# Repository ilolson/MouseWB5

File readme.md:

# MouseWB5 
40mm x 65.5mm Mini RC car inspired by half size micro mouse.
It is powered by the STM32WB5 precertified wireless module.
It uses STSPIN240 motor drivers to power four small coreless DC motors.
Contains the LSM6DSO as an IMU, and has headers for an additional fan motor for a suction mechanism.
SPI and I2C module connections for future VL53 lidar sensors, as well as programmable drift lights and turn signals. 
Includes a battery charging circuit and can be programmed via the TC2030 debug connector.

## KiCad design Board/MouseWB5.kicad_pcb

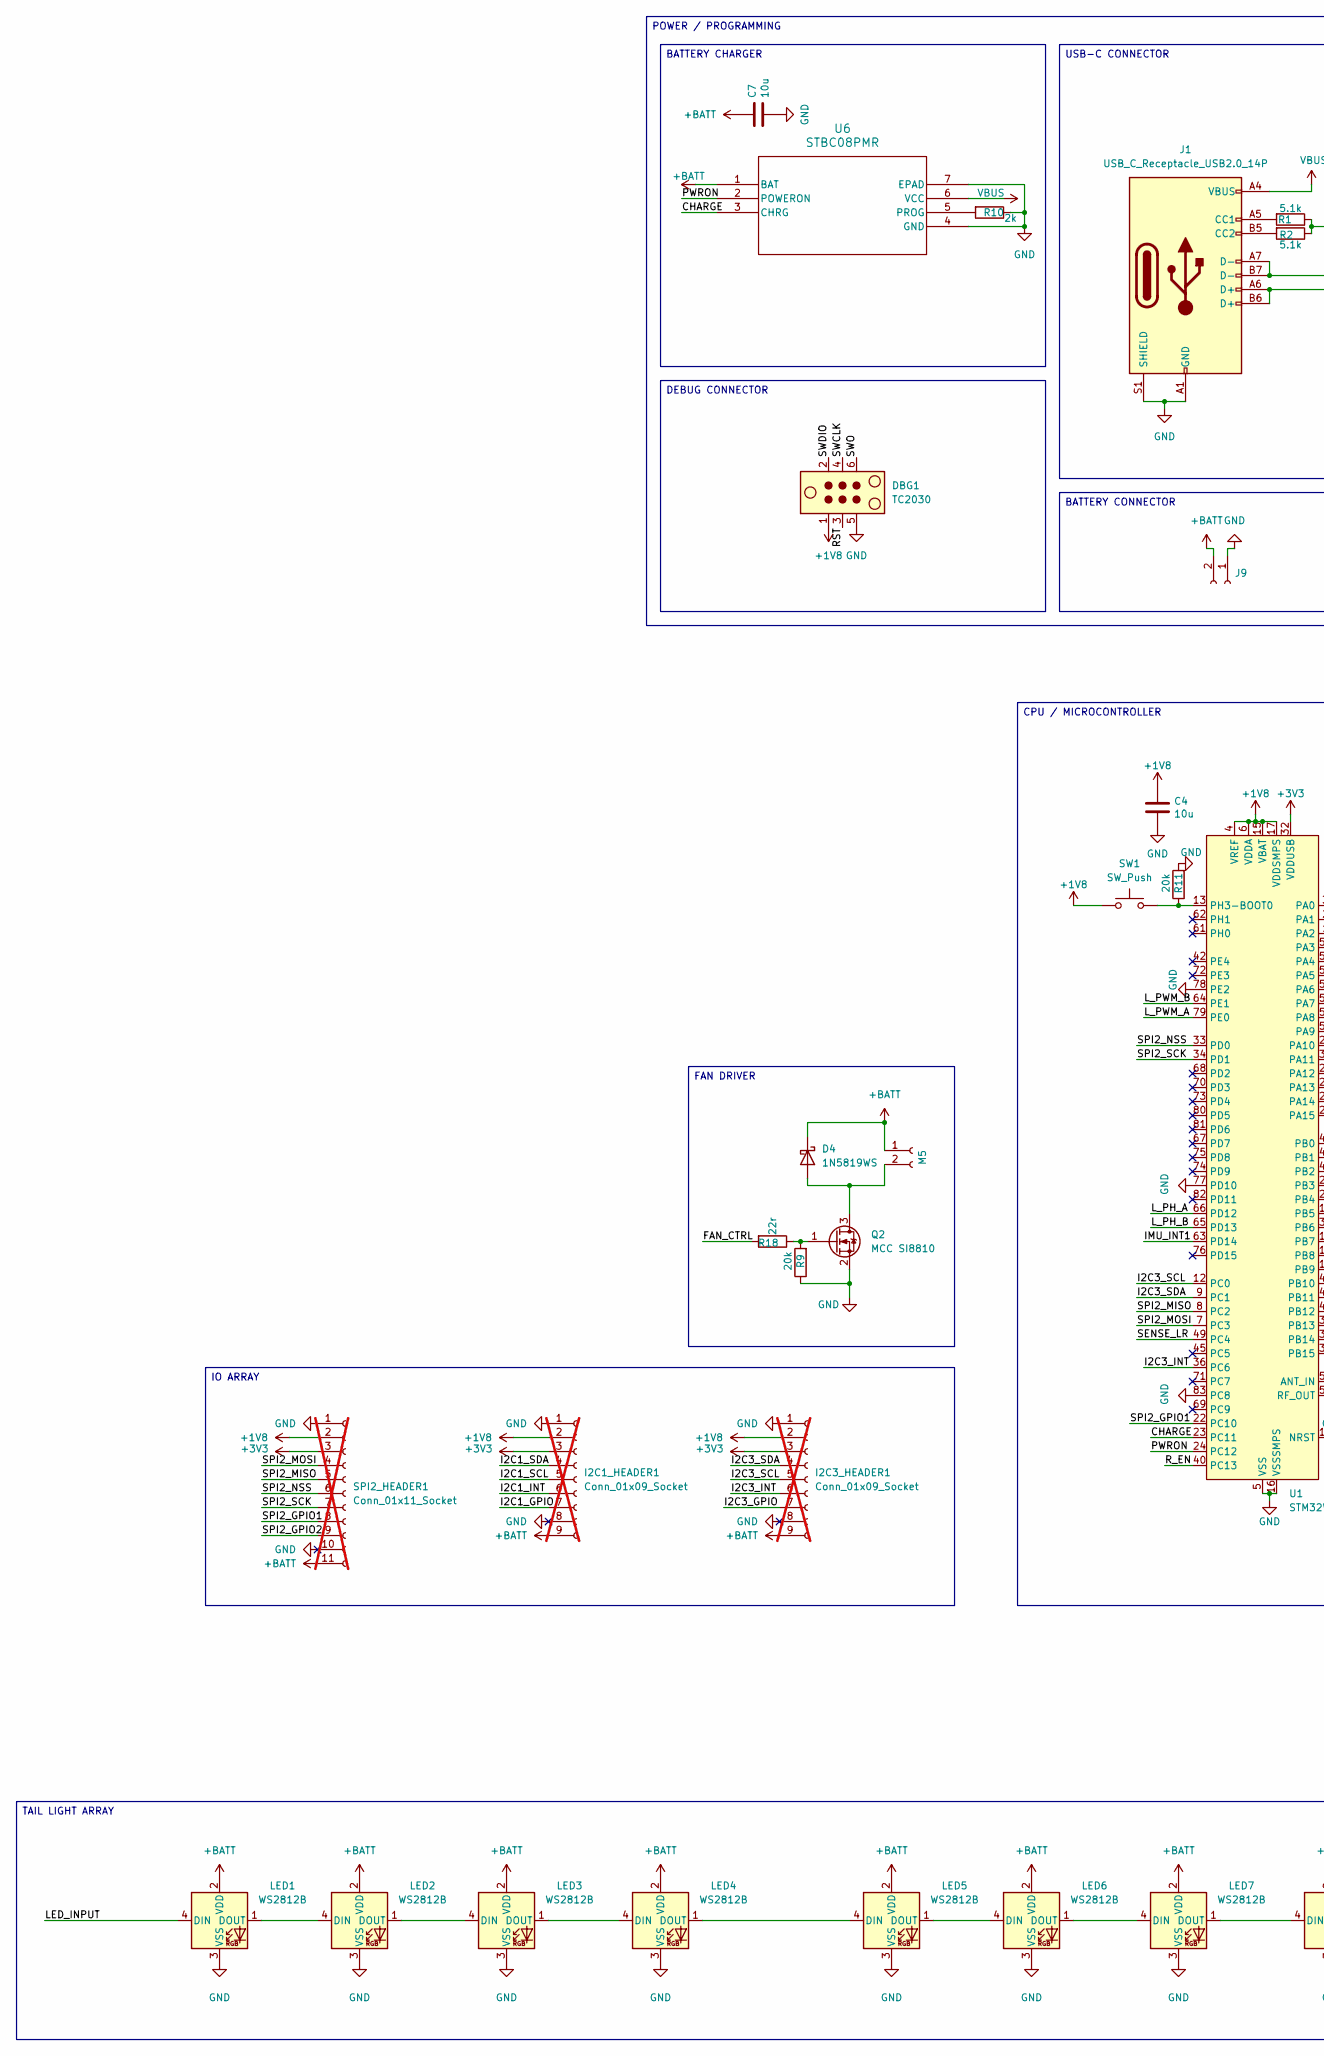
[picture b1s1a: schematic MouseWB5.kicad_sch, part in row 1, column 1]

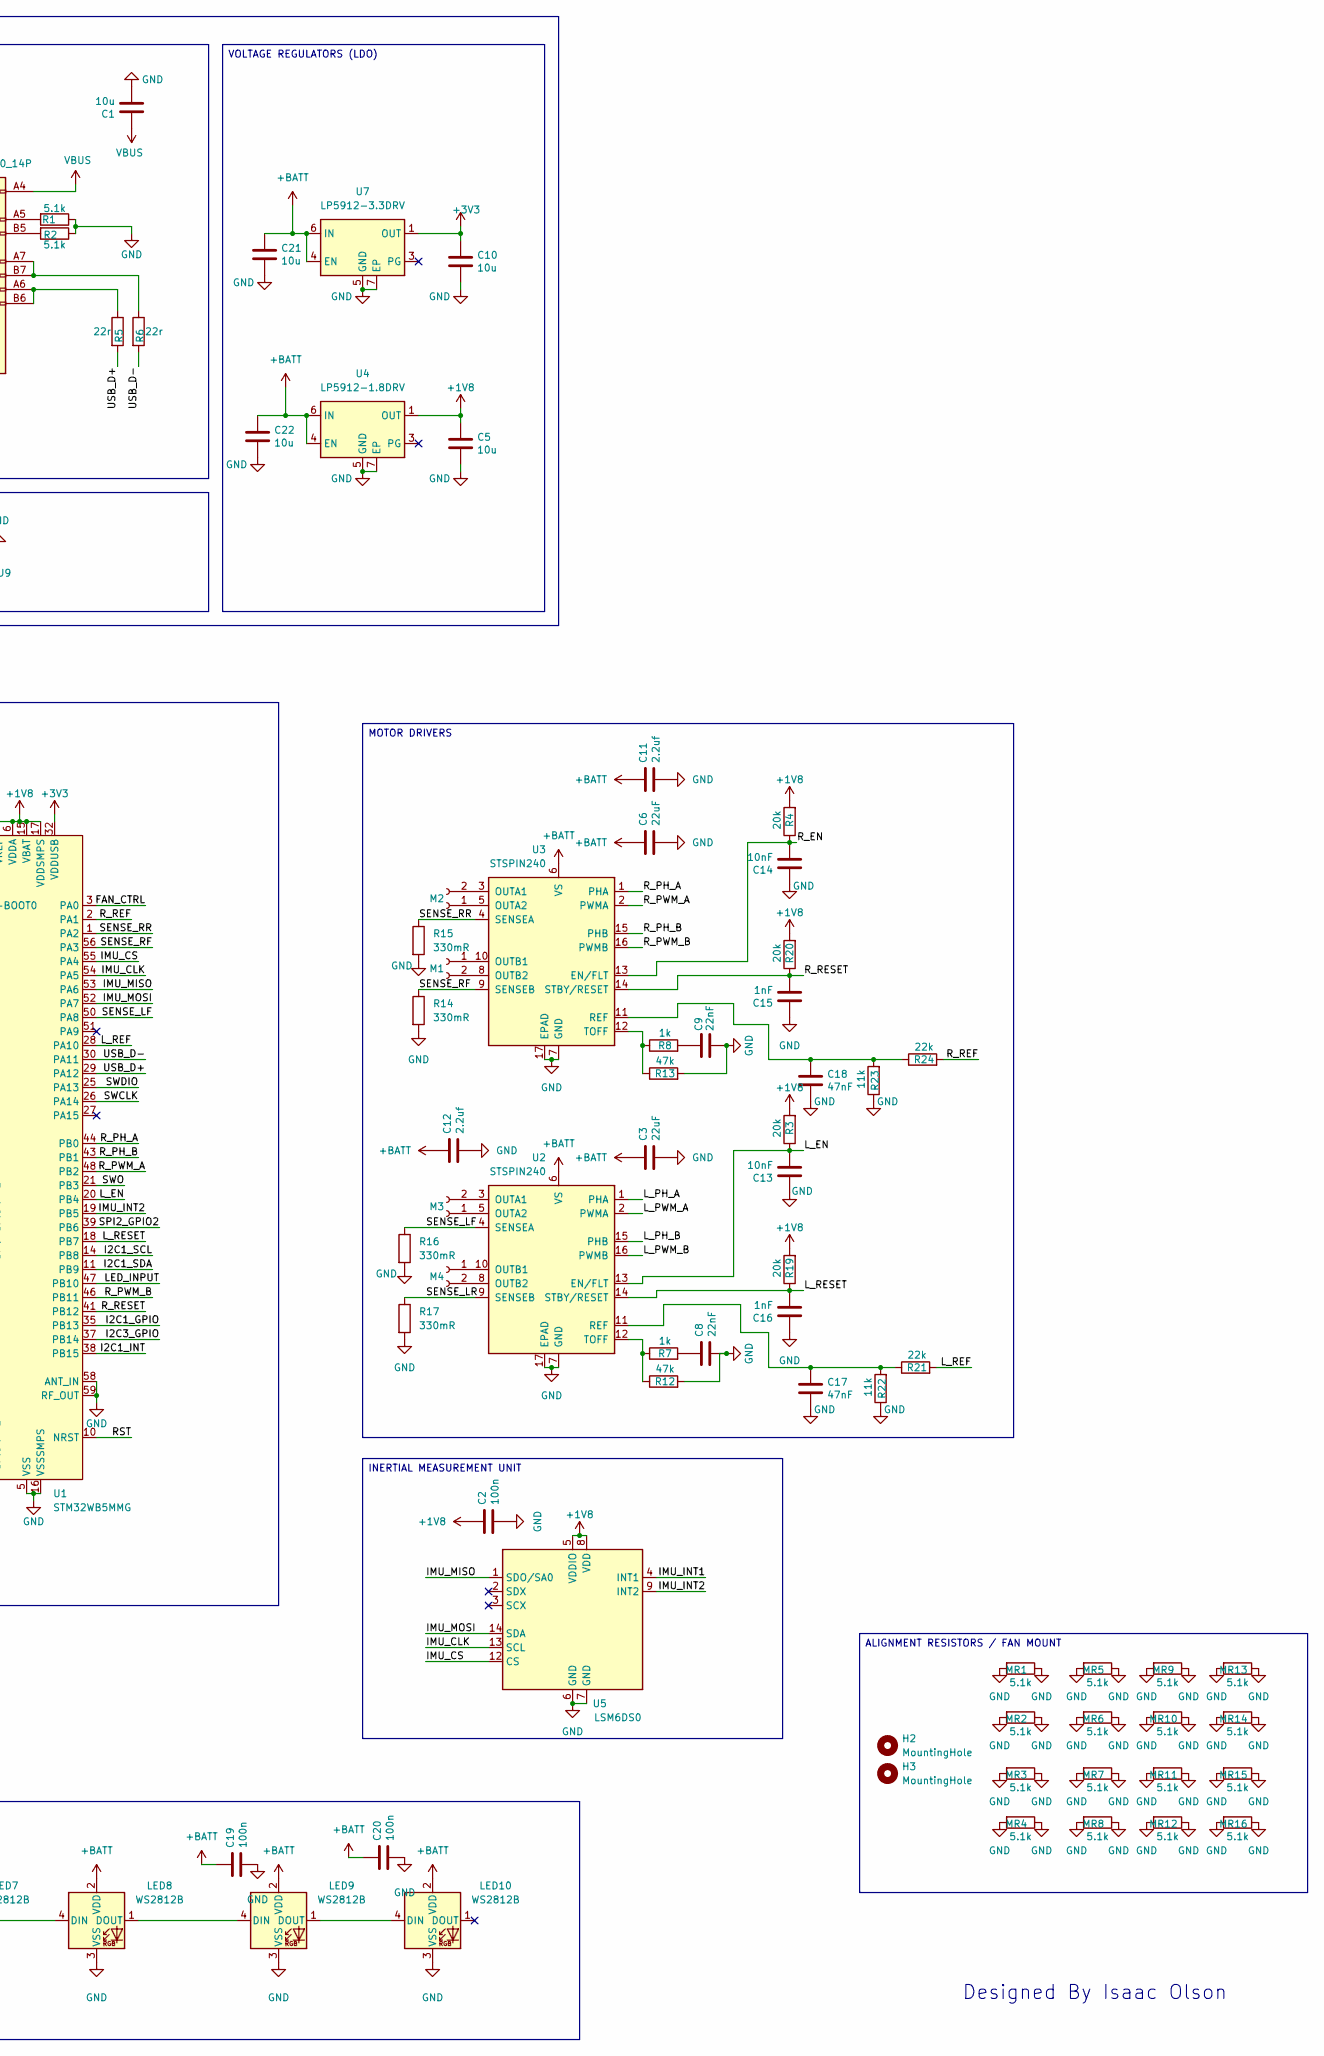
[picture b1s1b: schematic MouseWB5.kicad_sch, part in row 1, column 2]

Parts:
C1, C4, C5, C7, C10, C21, C22: 10u; C_0805_2012Metric; LCSC C408141
C2, C19, C20: 100n; C_0402_1005Metric; LCSC C1525
C3, C6: 22uF; C_0805_2012Metric; LCSC C602037
C8, C9: 22nF; C_0402_1005Metric; LCSC C337699
C11, C12: 2.2uf; C_0402_1005Metric; LCSC C170151
C13, C14: 10nF; C_0402_1005Metric; LCSC C15195
C15, C16: 1nF; C_0402_1005Metric; LCSC C77018
C17, C18: 47nF; C_0402_1005Metric; LCSC C82219
D4: 1N5819WS; D_SOD-323; LCSC C191023
DBG1: TC2030; Tag-Connect_TC2030-IDC-NL_2x03_P1.27mm_Vertical
H2, H3: MountingHole; MountingHole_2.1mm
I2C1_HEADER1, I2C3_HEADER1: Conn_01x09_Socket; PinHeader_1x09_P1.00mm_Vertical; not fitted
J1: USB_C_Receptacle_USB2.0_14P; USB_C_Receptacle_HRO_TYPE-C-31-M-12; LCSC C165948
J9: Conn_01x02_Socket; JST_GH_BM02B-GHS-TBT_1x02-1MP_P1.25mm_Vertical; LCSC C161690
LED1, LED2, LED3, LED4, LED5, LED6, LED7, LED8: WS2812B; LED-SMD_4P-L1.0-W1.0-TL_XL-1010RGBC-WS2812B; LCSC C5349953
LED9, LED10: WS2812B; 1010ws2812; LCSC C5349953
M1, M2, M3, M4, M5: Conn_01x02_Socket; JST_GH_BM02B-GHS-TBT_1x02-1MP_P1.25mm_Vertical; LCSC C161690
MR1, MR2, MR3, MR4, MR5, MR6, MR7, MR8, MR9, MR10, MR11, MR12, MR13, MR14, MR15, MR16: 5.1k; R_0402_1005Metric; LCSC C105872
Q2: MCC SI8810; SOT-23; LCSC C669009
R1, R2: 5.1k; R_0402_1005Metric; LCSC C105872
R3, R4, R9, R11, R19, R20: 20k; R_0402_1005Metric; LCSC C93942
R5, R6, R18: 22r; R_0201_0603Metric; LCSC C270355
R7, R8: 1k; R_0402_1005Metric; LCSC C106235
R10: 2k; R_0402_1005Metric; LCSC C4109
R12, R13: 47k; R_0402_1005Metric; LCSC C93943
R14, R15, R16, R17: 330mR; R_1206_3216Metric_Pad1.30x1.75mm_HandSolder; LCSC C2932844
R21, R24: 22k; R_0402_1005Metric; LCSC C82868
R22, R23: 11k; R_0402_1005Metric; LCSC C25749
SPI2_HEADER1: Conn_01x11_Socket; PinHeader_1x11_P1.00mm_Vertical; not fitted
SW1: SW_Push; TS-1088-AR02016; LCSC C455280
U1: STM32WB5MMG; ST-SiP-LGA-86-11x7.3mm; LCSC C5184586
U2, U3: STSPIN240; VQFN-16-1EP_3x3mm_P0.5mm_EP1.8x1.8mm; LCSC C962258
U4: LP5912-1.8DRV; WSON-6-1EP_2x2mm_P0.65mm_EP1x1.6mm_ThermalVias; LCSC C2876234
U5: LSM6DS0; LGA-14_3x2.5mm_P0.5mm_LayoutBorder3x4y; LCSC C481766
U6: STBC08PMR; DFN6_3X3_STM; LCSC C262929
U7: LP5912-3.3DRV; WSON-6-1EP_2x2mm_P0.65mm_EP1x1.6mm_ThermalVias; LCSC C524780

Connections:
+1V8: C2.1, C4.1, C5.1, DBG1.1, I2C1_HEADER1.2, I2C3_HEADER1.2, R3.2, R4.2, R19.2, R20.2, SPI2_HEADER1.2, SW1.1, U1.4 (VREF), U1.6 (VDDA), U1.15 (VBAT), U1.17 (VDDSMPS), U4.1 (OUT), U5.5 (VDDIO), U5.8 (VDD)
+3V3: C10.1, I2C1_HEADER1.3, I2C3_HEADER1.3, SPI2_HEADER1.3, U1.32 (VDDUSB), U7.1 (OUT)
+BATT: C3.1, C6.1, C7.1, C11.1, C12.1, C19.1, C20.1, C21.1, C22.1, D4.1 (K), I2C1_HEADER1.9, I2C3_HEADER1.9, J9.2, LED1.2 (VDD), LED2.2 (VDD), LED3.2 (VDD), LED4.2 (VDD), LED5.2 (VDD), LED6.2 (VDD), LED7.2 (VDD), LED8.2 (VDD), LED9.2 (VDD), LED10.2 (VDD), M5.1, SPI2_HEADER1.11, U2.6 (VS), U3.6 (VS), U4.4 (EN), U4.6 (IN), U6.1 (BAT), U7.4 (EN), U7.6 (IN)
/CHARGE: U1.23 (PC11), U6.3 (CHRG)
/FAN_CTRL: R18.2, U1.3 (PA0)
/I2C1_GPIO: I2C1_HEADER1.7, U1.35 (PB13)
/I2C1_INT: I2C1_HEADER1.6, U1.38 (PB15)
/I2C1_SCL: I2C1_HEADER1.5, U1.14 (PB8)
/I2C1_SDA: I2C1_HEADER1.4, U1.11 (PB9)
/I2C3_GPIO: I2C3_HEADER1.7, U1.37 (PB14)
/I2C3_INT: I2C3_HEADER1.6, U1.36 (PC6)
/I2C3_SCL: I2C3_HEADER1.5, U1.12 (PC0)
/I2C3_SDA: I2C3_HEADER1.4, U1.9 (PC1)
/IMU_CLK: U1.54 (PA5), U5.13 (SCL)
/IMU_CS: U1.55 (PA4), U5.12 (CS)
/IMU_INT1: U1.63 (PD14), U5.4 (INT1)
/IMU_INT2: U1.19 (PB5), U5.9 (INT2)
/IMU_MISO: U1.53 (PA6), U5.1 (SDO/SA0)
/IMU_MOSI: U1.52 (PA7), U5.14 (SDA)
/LED_INPUT: LED1.4 (DIN), U1.47 (PB10)
/L_EN: C13.2, R3.1, U1.20 (PB4), U2.13 (EN/FLT)
/L_PH_A: U1.66 (PD12), U2.1 (PHA)
/L_PH_B: U1.65 (PD13), U2.15 (PHB)
/L_PWM_A: U1.79 (PE0), U2.2 (PWMA)
/L_PWM_B: U1.64 (PE1), U2.16 (PWMB)
/L_REF: R21.2, U1.28 (PA10)
/L_RESET: C16.2, R19.1, U1.18 (PB7), U2.14 (STBY/RESET)
/PWRON: U1.24 (PC12), U6.2 (POWERON)
/RST: DBG1.3, U1.10 (NRST)
/R_EN: C14.2, R4.1, U1.40 (PC13), U3.13 (EN/FLT)
/R_PH_A: U1.44 (PB0), U3.1 (PHA)
/R_PH_B: U1.43 (PB1), U3.15 (PHB)
/R_PWM_A: U1.48 (PB2), U3.2 (PWMA)
/R_PWM_B: U1.46 (PB11), U3.16 (PWMB)
/R_REF: R24.2, U1.2 (PA1)
/R_RESET: C15.2, R20.1, U1.41 (PB12), U3.14 (STBY/RESET)
/SENSE_LF: R16.1, U1.50 (PA8), U2.4 (SENSEA)
/SENSE_LR: R17.1, U1.49 (PC4), U2.9 (SENSEB)
/SENSE_RF: R14.1, U1.56 (PA3), U3.9 (SENSEB)
/SENSE_RR: R15.1, U1.1 (PA2), U3.4 (SENSEA)
/SPI2_GPIO1: SPI2_HEADER1.8, U1.22 (PC10)
/SPI2_GPIO2: SPI2_HEADER1.9, U1.39 (PB6)
/SPI2_MISO: SPI2_HEADER1.5, U1.8 (PC2)
/SPI2_MOSI: SPI2_HEADER1.4, U1.7 (PC3)
/SPI2_NSS: SPI2_HEADER1.6, U1.33 (PD0)
/SPI2_SCK: SPI2_HEADER1.7, U1.34 (PD1)
/SWCLK: DBG1.4, U1.26 (PA14)
/SWDIO: DBG1.2, U1.25 (PA13)
/SWO: DBG1.6, U1.21 (PB3)
/USB_D+: R5.2, U1.29 (PA12)
/USB_D-: R6.2, U1.30 (PA11)
GND: C1.2, C2.2, C3.2, C4.2, C5.2, C6.2, C7.2, C8.2, C9.2, C10.2, C11.2, C12.2, C13.1, C14.1, C15.1, C16.1, C17.2, C18.2, C19.2, C20.2, C21.2, C22.2, DBG1.5, I2C1_HEADER1.1, I2C1_HEADER1.8, I2C3_HEADER1.1, I2C3_HEADER1.8, J1.A1 (GND), J1.A12 (GND), J1.B1 (GND), J1.B12 (GND), J1.S1 (SHIELD), J9.1, LED1.3 (VSS), LED2.3 (VSS), LED3.3 (VSS), LED4.3 (VSS), LED5.3 (VSS), LED6.3 (VSS), LED7.3 (VSS), LED8.3 (VSS), LED9.3 (VSS), LED10.3 (VSS), MR1.1, MR1.2, MR2.1, MR2.2, MR3.1, MR3.2, MR4.1, MR4.2, MR5.1, MR5.2, MR6.1, MR6.2, MR7.1, MR7.2, MR8.1, MR8.2, MR9.1, MR9.2, MR10.1, MR10.2, MR11.1, MR11.2, MR12.1, MR12.2, MR13.1, MR13.2, MR14.1, MR14.2, MR15.1, MR15.2, MR16.1, MR16.2, Q2.2 (S), R1.1, R2.1, R9.1, R10.1, R11.2, R12.2, R13.2, R14.2, R15.2, R16.2, R17.2, R22.1, R23.1, SPI2_HEADER1.1, SPI2_HEADER1.10, U1.5 (VSS), U1.16 (VSSSMPS), U1.31 (VSS), U1.57 (VSS), U1.58 (ANT_IN), U1.59 (RF_OUT), U1.60 (VSS), U1.77 (PD10), U1.78 (PE2), U1.83 (PC8), U1.84 (VSS), U1.86 (VSS), U2.7 (GND), U2.17 (EPAD), U3.7 (GND), U3.17 (EPAD), U4.5 (GND), U4.7 (EP), U5.6 (GND), U5.7 (GND), U6.4 (GND), U6.7 (EPAD), U7.5 (GND), U7.7 (EP)
unnamed: C8.1, R7.2
unnamed: C9.1, R8.2
unnamed: D4.2 (A), M5.2, Q2.3 (D)
unnamed: J1.A5 (CC1), R1.2
unnamed: J1.B5 (CC2), R2.2
unnamed: J1.A6 (D+), J1.B6 (D+), R5.1
unnamed: J1.A7 (D-), J1.B7 (D-), R6.1
unnamed: LED1.1 (DOUT), LED2.4 (DIN)
unnamed: LED2.1 (DOUT), LED3.4 (DIN)
unnamed: LED3.1 (DOUT), LED4.4 (DIN)
unnamed: LED4.1 (DOUT), LED5.4 (DIN)
unnamed: LED5.1 (DOUT), LED6.4 (DIN)
unnamed: LED6.1 (DOUT), LED7.4 (DIN)
unnamed: LED7.1 (DOUT), LED8.4 (DIN)
unnamed: LED8.1 (DOUT), LED9.4 (DIN)
unnamed: LED9.1 (DOUT), LED10.4 (DIN)
unnamed: M1.1, U3.10 (OUTB1)
unnamed: M1.2, U3.8 (OUTB2)
unnamed: M2.1, U3.5 (OUTA2)
unnamed: M2.2, U3.3 (OUTA1)
unnamed: M3.1, U2.5 (OUTA2)
unnamed: M3.2, U2.3 (OUTA1)
unnamed: M4.1, U2.10 (OUTB1)
unnamed: M4.2, U2.8 (OUTB2)
unnamed: Q2.1 (G), R9.2, R18.1
unnamed: R11.1, SW1.2, U1.13 (PH3-BOOT0)
unnamed: C17.1, R21.1, R22.2, U2.11 (REF)
unnamed: R7.1, R12.1, U2.12 (TOFF)
unnamed: C18.1, R23.2, R24.1, U3.11 (REF)
unnamed: R8.1, R13.1, U3.12 (TOFF)
unnamed: R10.2, U6.5 (PROG)
VBUS: C1.1, J1.A4 (VBUS), J1.A9 (VBUS), J1.B4 (VBUS), J1.B9 (VBUS), U6.6 (VCC)

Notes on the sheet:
Designed By Isaac Olson
ALIGNMENT RESISTORS / FAN MOUNT
MOTOR DRIVERS
CPU / MICROCONTROLLER
INERTIAL MEASUREMENT UNIT
VOLTAGE REGULATORS (LDO)
POWER / PROGRAMMING
BATTERY CONNECTOR
USB-C CONNECTOR
TAIL LIGHT ARRAY
BATTERY CHARGER
FAN DRIVER
IO ARRAY
DEBUG CONNECTOR

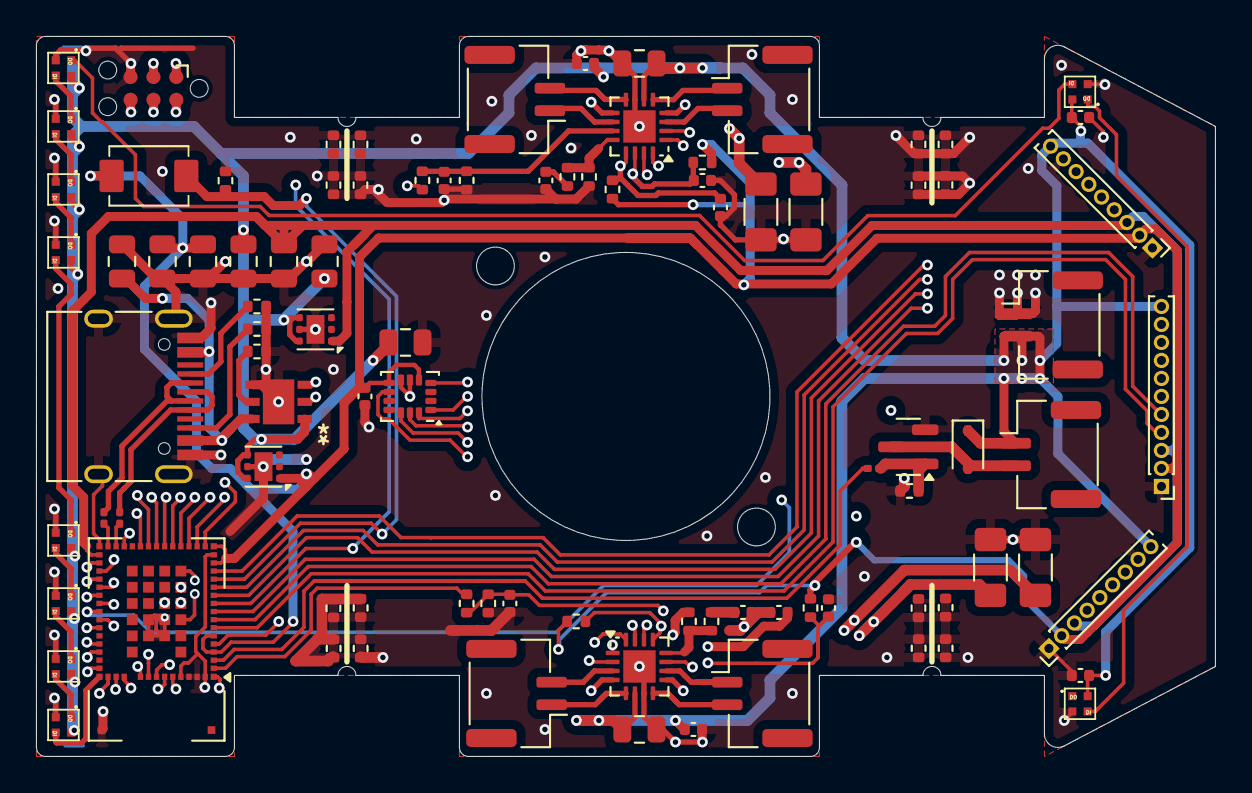
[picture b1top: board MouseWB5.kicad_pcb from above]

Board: 6 copper layers, 65.5 x 40.0 mm, 95 parts (0 on the bottom side), 84 nets.

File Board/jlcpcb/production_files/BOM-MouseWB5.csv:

Comment,Designator,Footprint,LCSC,Quantity
100n,"C19,C2,C20",C_0402_1005Metric,C1525,3
10nF,"C13,C14",C_0402_1005Metric,C15195,2
10u,"C1,C10,C21,C22,C4,C5,C7",C_0805_2012Metric,C408141,7
11k,"R22,R23",R_0402_1005Metric,C25749,2
1N5819WS,D4,D_SOD-323,C191023,1
1k,"R7,R8",R_0402_1005Metric,C106235,2
1nF,"C15,C16",C_0402_1005Metric,C77018,2
2.2uf,"C11,C12",C_0402_1005Metric,C170151,2
20k,"R11,R19,R20,R3,R4,R9",R_0402_1005Metric,C93942,6
22k,"R21,R24",R_0402_1005Metric,C82868,2
22nF,"C8,C9",C_0402_1005Metric,C337699,2
22r,"R18,R5,R6",R_0201_0603Metric,C270355,3
22uF,"C3,C6",C_0805_2012Metric,C602037,2
2k,R10,R_0402_1005Metric,C4109,1
330mR,"R14,R15,R16,R17",R_1206_3216Metric_Pad1.30x1.75mm_HandSolder,C2932844,4
47k,"R12,R13",R_0402_1005Metric,C93943,2
47nF,"C17,C18",C_0402_1005Metric,C82219,2
5.1k,"MR1,MR10,MR11,MR12,MR13,MR14,MR15,MR16,MR2,MR3,MR4,MR5,MR6,MR7,MR8,MR9,R1,R2",R_0402_1005Metric,C105872,18
Conn_01x02_Socket,"J9,M1,M2,M3,M4,M5",JST_GH_BM02B-GHS-TBT_1x02-1MP_P1.25mm_Vertical,C161690,6
LP5912-1.8DRV,U4,WSON-6-1EP_2x2mm_P0.65mm_EP1x1.6mm_ThermalVias,C2876234,1
LP5912-3.3DRV,U7,WSON-6-1EP_2x2mm_P0.65mm_EP1x1.6mm_ThermalVias,C524780,1
LSM6DS0,U5,LGA-14_3x2.5mm_P0.5mm_LayoutBorder3x4y,C481766,1
MCC SI8810,Q2,SOT-23,C669009,1
STBC08PMR,U6,DFN6_3X3_STM,C262929,1
STM32WB5MMG,U1,ST-SiP-LGA-86-11x7.3mm,C5184586,1
STSPIN240,"U2,U3",VQFN-16-1EP_3x3mm_P0.5mm_EP1.8x1.8mm,C962258,2
SW_Push,SW1,TS-1088-AR02016,C455280,1
USB_C_Receptacle_USB2.0_14P,J1,USB_C_Receptacle_HRO_TYPE-C-31-M-12,C165948,1
WS2812B,"LED1,LED10,LED2,LED3,LED4,LED5,LED6,LED7,LED8,LED9",LED-SMD_4P-L1.0-W1.0-TL_XL-1010RGBC-WS2812B,C5349953,10

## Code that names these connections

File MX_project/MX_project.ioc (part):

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Mcu.Name=STM32WB5MMGHx
Mcu.Package=LGA86
Mcu.UserName=STM32WB5MMGHx
PA0.GPIOParameters=GPIO_Label
PA0.GPIO_Label=FAN_CTRL
PA0.Signal=S_TIM2_CH1
PA1.GPIOParameters=GPIO_Label
PA1.GPIO_Label=R_REF
PA1.Signal=S_TIM2_CH2
PA10.GPIOParameters=GPIO_Label
PA10.GPIO_Label=L_REF
PA10.Signal=S_TIM1_CH3
PA11.Mode=Device
PA11.Signal=USB_DM
PA12.Mode=Device
PA12.Signal=USB_DP
PA13.GPIOParameters=GPIO_Label
PA13.GPIO_Label=SWDIO
PA13.Signal=SYS_JTMS-SWDIO
PA14.GPIOParameters=GPIO_Label
PA14.GPIO_Label=SWCLK
PA14.Signal=SYS_JTCK-SWCLK
PA2.GPIOParameters=GPIO_Label
PA2.GPIO_Label=SENSE_RR
PA2.Signal=ADCx_IN7
PA3.GPIOParameters=GPIO_Label
PA3.GPIO_Label=SENSE_RF
PA3.Signal=ADCx_IN8
PA4.Signal=SPI1_NSS
PA5.Signal=SPI1_SCK
PA6.Signal=SPI1_MISO
PA7.Signal=SPI1_MOSI
PA8.GPIOParameters=GPIO_Label
PA8.GPIO_Label=SENSE_LF
PA8.Signal=ADCx_IN15
PB0.GPIOParameters=GPIO_Label
PB0.GPIO_Label=R_PH_A
PB0.Signal=GPIO_Output
PB1.GPIOParameters=GPIO_Label
PB1.GPIO_Label=R_PH_B
PB1.Signal=GPIO_Output
PB10.GPIOParameters=GPIO_Label
PB10.GPIO_Label=WS2812_LED
PB10.Signal=S_TIM2_CH3
PB11.GPIOParameters=GPIO_Label
PB11.GPIO_Label=R_PWM_B
PB11.Signal=S_TIM2_CH4
PB12.GPIOParameters=GPIO_Label
PB12.GPIO_Label=R_RESET
PB12.Signal=GPIO_Output
PB13.GPIOParameters=GPIO_Label
PB13.GPIO_Label=TURN_L
PB13.Signal=TIM1_CH1N
PB14.GPIOParameters=GPIO_Label
PB14.GPIO_Label=TURN_R
PB14.Signal=TIM1_CH2N
PB15.GPIOParameters=GPIO_Label
PB15.GPIO_Label=I2C1_INT
PB15.Signal=GPIO_Output
PB2.GPIOParameters=GPIO_Label
PB2.GPIO_Label=R_PWM_A
PB2.Signal=LPTIM1_OUT
PB3.GPIOParameters=GPIO_Label
PB3.GPIO_Label=SWO
PB3.Signal=SYS_JTDO-SWO
PB4.GPIOParameters=GPIO_Label
PB4.GPIO_Label=L_EN
PB4.Signal=GPIO_Output
PB5.GPIOParameters=GPIO_Label
PB5.GPIO_Label=IMU_INT1
PB5.Signal=GPIO_Input
PB6.GPIOParameters=GPIO_Label
PB6.GPIO_Label=SPI2_GPIO2
PB6.Signal=GPIO_Output
PB7.GPIOParameters=GPIO_Label
PB7.GPIO_Label=L_RESET
PB7.Signal=GPIO_Output
PB8.Signal=I2C1_SCL
PB9.Signal=I2C1_SDA
PC0.Signal=I2C3_SCL
PC1.Signal=I2C3_SDA
PC10.Signal=GPIO_Output
PC11.GPIOParameters=GPIO_Label
PC11.GPIO_Label=CHARGE
PC11.Signal=GPIO_Input
PC12.GPIOParameters=GPIO_Label
PC12.GPIO_Label=PWRON
PC12.Signal=GPIO_Input
PC13.GPIOParameters=GPIO_Label
PC13.GPIO_Label=R_EN
PC13.Signal=GPIO_Output
PC2.Signal=SPI2_MISO
PC3.Signal=SPI2_MOSI
PC4.GPIOParameters=GPIO_Label
PC4.GPIO_Label=SENSE_LR
PC4.Signal=ADCx_IN13
PC6.GPIOParameters=GPIO_Label
PC6.GPIO_Label=I2C3_INT
PC6.Signal=GPIO_Output
PD0.Signal=SPI2_NSS
PD1.Signal=SPI2_SCK
PD12.GPIOParameters=GPIO_Label
PD12.GPIO_Label=L_PH_A
PD12.Signal=GPIO_Output
PD13.GPIOParameters=GPIO_Label
PD13.GPIO_Label=L_PH_B
PD13.Signal=GPIO_Output
PD14.GPIOParameters=GPIO_Label
PD14.GPIO_Label=IMU_INT1
PD14.Signal=GPIO_Input
PE0.GPIOParameters=GPIO_Label
PE0.GPIO_Label=L_PWM_A
PE0.Signal=S_TIM16_CH1
PE1.GPIOParameters=GPIO_Label
PE1.GPIO_Label=L_PWM_B
PE1.Signal=S_TIM17_CH1
PH3-BOOT0.GPIOParameters=GPIO_Label
PH3-BOOT0.GPIO_Label=BOOT
PH3-BOOT0.Signal=GPIO_Input
RCC.HSE_VALUE=32000000
RCC.SYSCLKFreq_VALUE=64000000
RCC.SYSCLKSource=RCC_SYSCLKSOURCE_PLLCLK
board=custom

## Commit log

2025-07-16 init
2025-07-16 work
2025-07-19 test
2025-09-14 exp3_done
2026-01-25 Revert "work"
    This reverts commit ebc5c044978ddb65968714e0a5620810b6ad0afb.
2026-01-25 holes
2026-01-26 retouchshuntR
2026-01-26 macfont
2026-02-02 real_order
2026-02-02 real_order2
